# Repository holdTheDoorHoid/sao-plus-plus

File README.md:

# SAO++

Classic Simple Add-Ons, rebuilt for today's badges and for real production runs, plus a growing set of new ones.

The repo holds two kinds of board, kept in separate folders:

- **Ports** (`boards/`): other makers' SAOs, rebuilt to the SAO++ standard with credit to the original maker.
- **SAO++ Originals** (`originals/`): LSOH's own designs, made for SAO++ from scratch.

SAO++ takes older SAOs (the little art boards that plug into conference badges), ports them to the **SAO v1.69bis** 6-pin standard, adds small improvements where they make sense, and publishes them openly. Every board shares the same connector, power switch, battery holder, and LED family, so they can be built side by side on the same reels and the same assembly setup.

## What every SAO++ board has

- **6-pin SAO v1.69bis connector**, surface-mount and shrouded, on the back. Nothing pokes through the art side.
- **SAO / OFF / BATTERY switch**: runs from the badge or from its own CR2032. It is wired so the badge can never charge the coin cell.
- **CR2032 coin cell**: several days of daytime wear on a simple LED board.
- **Boards that need a chip** use a Seeed Studio XIAO ESP32 module instead of a coin cell: the same switch chooses between badge power and the module's own (USB-C or a LiPo).
- **LEDs on the back**: side-firing ones that light the art from the edges, or reverse-mount ones that shine through the board.
- **All parts on the back**; the front is pure art.

The full rules are in [docs/standard.md](docs/standard.md), and the shared parts with live prices are in [docs/parts.md](docs/parts.md).

## Layout

```
boards/<slug>/        one folder per PORT of another maker's SAO
originals/<slug>/     one folder per SAO++ ORIGINAL (LSOH's own design); same layout as a port
  board.yml           provenance, license, permission, features, shared parts used
  README.md           credit to the original maker, what changed, build notes
  hardware/           KiCad 10 project
  art/                source artwork
  production/         Gerbers, drill, BOM and placement files for one board and for a panel
  firmware/           only for boards with a microcontroller
boards/_template/     copy this to start a new board
lib/                  shared KiCad symbols, footprints, 3D models, power block, starter project
docs/                 house standard, approved parts, porting and permission guide
tools/                check_boards.py (paperwork check, runs on every push), gen_footprints.py, saopp_symbols.py,
                      gen_schematic.py, extract_outline.py, saopp_board.py (helpers for each board's build script), panelize.py, export_fab.py
```

## Ports

Other makers' SAOs, rebuilt. Credit and permission status are in each board's README.

| Board | Original maker | Status |
|---|---|---|
| [Fat Pika](boards/fat-pika/) | TwinkleTwinkie (DEF CON 26, 2018) | Designed and rule-checked, not yet built. **Permission pending: not open-licensed**, see the board README |
| [Mad Cat](boards/mad-cat/) | TwinkleTwinkie (DEF CON 26, 2018) | Designed and rule-checked, not yet built. **Permission pending: not open-licensed**, see the board README |
| [Big Green](boards/big-green/) | TwinkleTwinkie (DEF CON 26, 2018) | Designed and rule-checked, not yet built. **Permission pending: not open-licensed**, see the board README |
| [La Bomba](boards/la-bomba/) | TwinkleTwinkie (DEF CON 26, 2018) | Designed and rule-checked, not yet built. **Permission pending: not open-licensed**, see the board README |
| [Nibbler](boards/nibbler/) | TwinkleTwinkie (DEF CON 26, 2018) | Designed and rule-checked, not yet built. **Permission pending: not open-licensed**, see the board README |
| [RBG](boards/rbg/) | lemons4all (DEF CON 26, 2018) | Designed and rule-checked, not yet built. **Permission pending: not open-licensed**, see the board README |
| [Frida](boards/frida/) | lemons4all (DEF CON 26, 2018) | Designed and rule-checked, not yet built. **Permission pending: not open-licensed**, see the board README |
| [Oh My Glob (LSP)](boards/lumpy/) | lemons4all (DEF CON 26, 2018) | Designed and rule-checked, not yet built; the tightest fit of the set (see its README). **Permission pending: not open-licensed** |
| [Hack-Man](boards/hack-man/) | InstantArcade (Bob), 2024 | Recreated from the maker's pictures (no files were published), rule-checked, not yet built. Seeed XIAO ESP32 controller, new Rust firmware. **Permission pending: not open-licensed**, see the board README |
| [Han SAOlo](boards/han-saolo/) | davedarko (2024) | Designed and rule-checked, not yet built. Short life and weak green/blue on a coin cell (calculated). **Permission pending: not open-licensed**, see the board README |
| [Knight Rider (K.I.T.T.)](boards/knight-rider/) | davedarko (2017) | Designed and rule-checked, not yet built. No firmware yet. **Permission pending: not open-licensed**, see the board README |
| [Soot Sprite](boards/soot-sprite/) | davedarko (2026) | Designed and rule-checked, not yet built. **Permission pending: not open-licensed**, see the board README |
| [COVID-19 Test](boards/covid-test/) | davedarko (2022) | Designed and rule-checked, not yet built. **Permission pending: not open-licensed**, see the board README |
| [Penghito Poco](boards/penghito-poco/) | davedarko (year not recorded) | Designed and rule-checked, not yet built. **Permission pending: not open-licensed**, see the board README |
| [Mysterio](boards/mysterio/) | davedarko (2025) | Designed and rule-checked, not yet built. Seeed XIAO ESP32 controller, new Rust firmware (never run on hardware). **Permission pending: not open-licensed**, see the board README |
| [Do Or Donut](boards/do-or-donut/) | davedarko (2019) | Designed and rule-checked, not yet built. Seeed XIAO ESP32 controller, new Rust firmware (never run on hardware). **Four-layer board.** **Permission pending: not open-licensed**, see the board README |
| [Vendetta](boards/vendetta/) | davedarko (2022) | Designed and rule-checked, not yet built. Scaled up 1.23x. **Permission pending: not open-licensed**, see the board README |
| [Hello My Name Is](boards/hello-my-name-is/) | davedarko (2024) | Designed and rule-checked, not yet built. Scaled up 1.1x. **Permission pending: not open-licensed**, see the board README |
| [LECCO postcard](boards/lecco/) | davedarko (2026) | Designed and rule-checked, not yet built. Scaled up 1.2x; badge power only (no cell or switch). **Permission pending: not open-licensed**, see the board README |
| [Sloth](boards/sloth/) | davedarko (2017) | Was a pin; now an SAO. Designed and rule-checked, not yet built. Scaled up 1.3x. No firmware yet. **Permission pending: not open-licensed**, see the board README |
| [Flux Capacitor](boards/flux-capacitor/) | davedarko (2017) | Was a pin; now an SAO. Designed and rule-checked, not yet built. Scaled up 1.35x. No firmware yet. **Permission pending: not open-licensed**, see the board README |
| [Retro Spacehuhn](boards/spacehuhn/) | davedarko (year not recorded) | Was a pin; now an SAO. Designed and rule-checked, not yet built. The chicken logo is Spacehuhn's. **Permission pending: not open-licensed**, see the board README |
| [Mr. Robot](boards/mr-robot/) | davedarko (2019) | Designed and rule-checked, not yet built. Scaled up 1.1x. Seeed XIAO ESP32 controller, new sounder driver, new Rust firmware (never run on hardware). **Permission pending: not open-licensed**, see the board README |
| [Nunchuck](boards/nunchuck/) | Andrew Geppert / ageppert (2024) | Designed and rule-checked, not yet built. Badge-driven adapter for a Wii Nunchuk: no chip, no switch, no cell. Rust host driver crate. MIT (open licence) |
| [Mad Cat Backpack](boards/mad-cat-backpack/) | Peter Shabino / Wireb (2018) | Designed and rule-checked, not yet built. Sits behind a bare SAO++ Mad Cat and animates its eyes and teeth. Seeed XIAO ESP32 controller, new Rust firmware (never run on hardware). MIT (open licence) |
| [Duck Bath](boards/duck-bath/) | Adrian Studer / astuder (2024) | Designed and rule-checked, not yet built. Scaled up 1.45x. Seeed XIAO ESP32 controller, new Rust firmware (never run on hardware). MIT (open licence) |
| [TARS](boards/tars/) | davedarko (2024) | Designed and rule-checked, not yet built. Display, touch slabs and speaker kept; Seeed XIAO ESP32 controller plus a touch chip, new Rust firmware (never run on hardware). MIT (open licence) |
| [Eggplant](boards/eggplant/) | Krux / Darknet Industries (2018) | Designed and rule-checked, not yet built. Scaled up 1.35x. Seeed XIAO ESP32 controller, new Rust firmware (never run on hardware). MIT (open licence) |

## SAO++ Originals

LSOH's own designs, under the SAO++ licences. None is built yet; the first shortlist of ten
cybersecurity-themed art boards is in [originals/README.md](originals/README.md).

## Adding a board

Read [docs/porting-guide.md](docs/porting-guide.md). In short: confirm the license or get the maker's permission **first**, copy `boards/_template` (into `originals/<slug>/` for an LSOH design, with `permission: own`), start from `lib/template`, and run `python3 tools/check_boards.py`.

## License

- Hardware designs: [CERN-OHL-S-2.0](LICENSE). Anyone can build and sell these; changes you distribute must stay open.
- Artwork: [CC-BY-SA-4.0](LICENSE-ART).
- **These licenses cover SAO++'s own work only**, which includes every board in `originals/` in full. A board marked "permission pending" in its README is not open-licensed: its original design and art stay with the original maker.
- Boards ported from other makers keep their credit, and their original license terms are recorded in each `board.yml`. Where a board's original license differs, its README says so and it takes precedence for that board.

Original designs remain credited to their makers. If you made one of these boards and want it changed or removed, open an issue.

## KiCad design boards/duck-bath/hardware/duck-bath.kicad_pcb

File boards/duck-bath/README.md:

# Duck Bath — SAO++ edition

Originally **duckBATH**, one of the two **duckGLOW** SAOs by **Adrian Studer (astuder)**, 2024: https://github.com/astuder/duckglow (write-up: https://hackaday.io/project/198918-duckglow-sao). A bathtub full of bubbles with a 5 mm RGB LED standing in the foam; a little rubber duck sits on the LED and glows. Its sister board, the shark-mouth **Duck Jaws**, is in [`../duck-jaws/`](../duck-jaws/).

> **Open licence — credit kept.** The maker's repository is MIT-licensed: "MIT License, Copyright (c) 2024 Adrian Studer". The same `LICENSE.md` also carries the full text of the CERN Open Hardware Licence v2 – Permissive (CERN-OHL-P), without saying which part applies to what; both are permissive. His licence file is kept unchanged in [`original/LICENSE.md`](original/LICENSE.md), and this note records what was changed (CERN-OHL-P section 3.3 asks for that): on 2026-11-11 the board was rebuilt for SAO++ as listed below, and the firmware was rewritten in Rust. Nothing else is needed before publishing.
>
> The art is the maker's own drawing; nothing on the board belongs to a third party. The rubber duck is a separate, bought toy.

The renders use green; the maker's boards are **white with black silkscreen** (see `production/README.md`).

## What changed from the original

| | Original (2024, v0.2) | SAO++ rev A |
|---|---|---|
| Size | 40.3 × 20.3 mm | **Scaled up 1.45×** (outline and drawing together): **58.1 × 29.0 mm** (see "Why it is 45 % bigger") |
| The LED | 5 mm RGB LED standing in the bubbles, legs soldered on the back | **Same LED, same footprint, true size**, centred where it was |
| Controller | WCH CH32V003 chip with a boost converter (runs from 2–3.3 V) | **Seeed Studio XIAO ESP32** module soldered flat on the back (C3, S3 or C6 all fit). Its USB-C socket comes out of the tub bottom, between the feet |
| Connector | 2×3 SMD pin header | 6-pin SAO v1.69bis, shrouded and keyed, under the LED, 5.7 mm left of the middle |
| Power | Badge only | Slide switch, knob out of the tub bottom: **SAO** / **OFF** / **USB-BAT** (USB-C, or a LiPo cell on the new JST-PH socket at the left wall, which the XIAO charges) |
| Front | Copper pour under the mask, silkscreen drawing of tub, bubbles and feet | All kept, scaled. Two 0.9 mm holes in the tub bottom (the switch's pegs), four small covered holes (ground vias) in the tub, and the tub bottom is cut flat by at most 0.5 mm over 11 mm under the switch so its knob sticks out |
| Back | Board name, I2C address and GPIO notes, address jumpers | Board name, "SAO++ rA", "Adrian Studer 2024", "NO USB ON SAO", switch ends (SAO / USB), "+"/"−" and "LiPo" at the socket, "1" at the connector |
| Dropped | — | CH32V003, boost converter (ME2188 + 22 µH + three 22 µF), reverse-polarity transistor, two 10 k I2C pull-ups (SAO++ boards leave the pull-ups to the badge), 1 k on GPIO1, 100 nF, two address jumpers, test pad |

**Parts shared with the rest of SAO++:** connector, switch, XIAO footprint, LiPo socket, 330 Ω resistor. **New, kept in this board's folder:** the maker's 5 mm RGB LED and his 100 Ω LED resistor (three of them). The 100 Ω is kept rather than the shared 330 Ω because green and blue need about 3 V: through 330 Ω from a 3.3 V rail they would barely glow. The LED itself has no part number in the maker's files: one must be picked (any 5 mm, 4-leg, common-anode RGB LED with legs in the order red, anode, green, blue).

## Why it is 45 % bigger (owner rule of 2026-11-12)

The maker's tub is 20 mm tall; the XIAO alone is 21 mm long and 18 mm wide, and its USB-C plug (about 12.4 mm wide) must reach a straight bit of edge. The only straight edges are the tub bottom between the feet and the short side walls. Tried in 5 % steps:

- USB-C out of a side wall: needs about 1.52×, and the rim's little bulge then blocks the plug.
- USB-C out of the bottom, module under the LED: needs 1.55× (the module must clear the LED's legs).
- **USB-C out of the bottom, module beside the LED: fits at 1.45×** with 0.2 mm to spare between the module and the LED's legs on one side and the plug and the right foot on the other. 1.40× does not fit.

The connector, switch and LiPo socket then fit beside it. Board area is 2.1× the original. Line widths only get thicker.

## How it is wired (all on the back, no signal vias)

Everything electrical is on the back copper; nothing but the maker's art is on the front. Three tricks keep it to one layer:

- **Under the module.** Two wires (SCL and GPIO2) slip between the XIAO's edge pads, 0.17 mm from each (as on Mr. Robot), and reach their pads from underneath, so they never cross SDA. The battery wire also runs under the module to its two pad sets.
- **Resistors as bridges.** The badge's 3.3 V runs between the pads of R4 (OFF sense), and the 3.3 V for the LED runs between the pads of R1 (red resistor).
- **Ground on the front.** The front copper (the maker's pour) is joined to ground through **four tented vias**, which also joins up the bits of back ground that the wires cut apart. They show as four tiny dots on the white tub, like the dots on the maker's own board.

## Pin map

| XIAO pin | Goes to |
|---|---|
| D10 | red: R1 100 Ω → LED red leg. Low = on |
| D8 | green: R2 100 Ω → LED green leg. Low = on |
| D7 | blue: R3 100 Ω → LED blue leg. Low = on |
| D4 / D5 | SAO SDA / SCL (no pull-ups on the board; the badge provides them). The XIAO is the badge's I2C target |
| D6 | SAO GPIO2 through 330 Ω (R6): WS2812 data from the badge, as on the maker's board |
| D1 | switch OFF sense, through R4 (330 Ω): high when the knob is on OFF |
| 3V3, GND | the board's 3.3 V rail (switch common, LED anode) and ground |
| BAT+ / BAT− (under the module, both positions) | the JST-PH LiPo socket |
| D0, D2, D3, D9, 5V | not connected |
| SAO GPIO1 | **not connected** (see below) |

**Why D7 and D8, and no SAO GPIO1.** Only D10 and D3 are free, non-start-up pins on all three modules, and the LED needs three. The LED sits right above the gap between the connector and the XIAO's left-hand pads, where SDA, SCL and GPIO2 already cross, so its wires go round the top of the module to the right-hand pads: D7, D8, D10 and 3V3, in that order. That takes D7, the house pin for SAO GPIO1. The maker used GPIO1 only to program his chip, so nothing is lost on this board. D8 is a start-up ("strapping") pin on the C3: the LED pulls it up weakly at power-on, which is the level the C3 wants, but see the checklist.

## Current budget (badge power)

| | About | Note |
|---|---|---|
| XIAO, radio off, 80 MHz | 20–25 mA (C3/C6), more on the S3 | the firmware never starts Wi-Fi or Bluetooth |
| Red at full | 13 mA | (3.3 V − 2.0 V) / 100 Ω; LED forward voltages are typical values, not measured |
| Green, blue at full | 3–4 mA each | they need about 3 V, so little current flows from 3.3 V |
| **All white, full** | **about 45 mA** | inside the 50 mA SAO++ budget, just |
| Maker's default animation | about 25–30 mA | red and green breathing up to 31 %, blue off |

## Firmware

New Rust firmware for the XIAO is in [`firmware/`](firmware/), shared with Duck Jaws (43 tests pass; builds for the C3, C6 and S3; **never run on a real board**). It keeps the maker's I2C register map (badge code written for his boards works), his fading animation and default colours, his WS2812 mode on GPIO2, and saving settings to flash. It answers at **0x22** (house numbering), or the maker's **0x6C** as a build option. See its README for what is the same and what is not.

## Things to check on the first prototype

1. **Badge power into the XIAO's 3V3 pin**: boots from a badge alone, nothing warm, current under 50 mA with the LED white.
2. **LED colours and brightness** through the rubber duck, with the maker's 100 Ω; the duck should glow as in the maker's photos.
3. **D8 at start-up (C3):** flashing over USB and normal start-up must still work with the green LED on D8. If holding BOOT while plugging in no longer enters download mode, D8 needs a pull-up (a 1.3 k from D8 to 3V3 would do, at the cost of 2.5 mA when green is on).
4. **The wires between the XIAO's pads** (0.17 mm gaps): check for solder bridges after assembly, as on Mr. Robot.
5. **USB-C plug fit** at the tub bottom: the socket sticks out about 0.5 mm past the edge at its middle; the plug must seat fully.
6. **Switch knob** at the flattened tub bottom: it should slide with a fingernail; if SAO and USB turn out swapped, the silkscreen is wrong, not the wiring.
7. **LiPo polarity**: the socket follows the Adafruit / SparkFun convention, "+" printed beside it.
8. **Connector position and pin 1** against a v1.69bis badge, and how the wider board hangs with the connector 5.7 mm left of centre.
9. **The four ground vias** on the front: should be barely visible on a white board.

## Files

- `hardware/duck-bath.kicad_pro`: KiCad 10 project. ERC: 0. DRC: 0 errors, 0 unconnected, schematic matches the board; 2 warnings (the LED's "B G + R" leg label touching the connector's unused pin 5, and one copper-sliver warning in the art).
- `hardware/circuit.json` (written by `make_circuit.py`): the circuit as data; `tools/gen_schematic.py duck-bath` and `build_board.py` both read it.
- `hardware/extract_art.py`: pulls the outline, the front drawing and the LED position out of the maker's KiCad 8 board into `hardware/art.json`.
- `hardware/build_board.py`: rebuilds the whole board in one run (about 30 s): placement, the hand-routed wires, the battery / 3.3 V / ground routing by `router.py` (a copy of Knight Rider's small grid router), ground copper, labels.
- `hardware/parts_local.py`, `hardware/make_local_footprints.py`, `hardware/duck-bath-local.pretty/`: the LED and the 100 Ω resistor.
- `hardware/duck-bath.kicad_dru`: the art rule, plus three small parts allowed inside bigger parts' courtyards (each with its real gap).
- `production/`: everything a board house needs. Start with [production/README.md](production/README.md).
- `original/`: the maker's untouched files: KiCad 8 design, firmware (C), examples, design SVGs, licence.

## Parts cost (parts only, LCSC list prices checked 2026-11-10 unless noted)

| Part | Qty | Each @ ~100 boards |
|---|---|---|
| Connector XFCN BH254VS-6P (C492445) | 1 | $0.12 |
| Switch C&K PCM13SMTR (Digikey) | 1 | ~$0.90 |
| LiPo socket JST S2B-PH-SM4-TB (C295747) | 1 | $0.16 |
| Resistor 330 Ω 0603 (C23138) | 2 | <$0.01 |
| Resistor 100 Ω 0603 (maker's C22775) | 3 | not priced (orchestrator to check) |
| 5 mm RGB LED, common anode | 1 | not chosen yet |
| **Total without the module, LED and 100 Ω** | | **about $1.20** |
| Seeed Studio XIAO ESP32-C3 / S3 / C6 | 1 | not priced here |

The bare board, the rubber duck and the optional LiPo cell are not included.

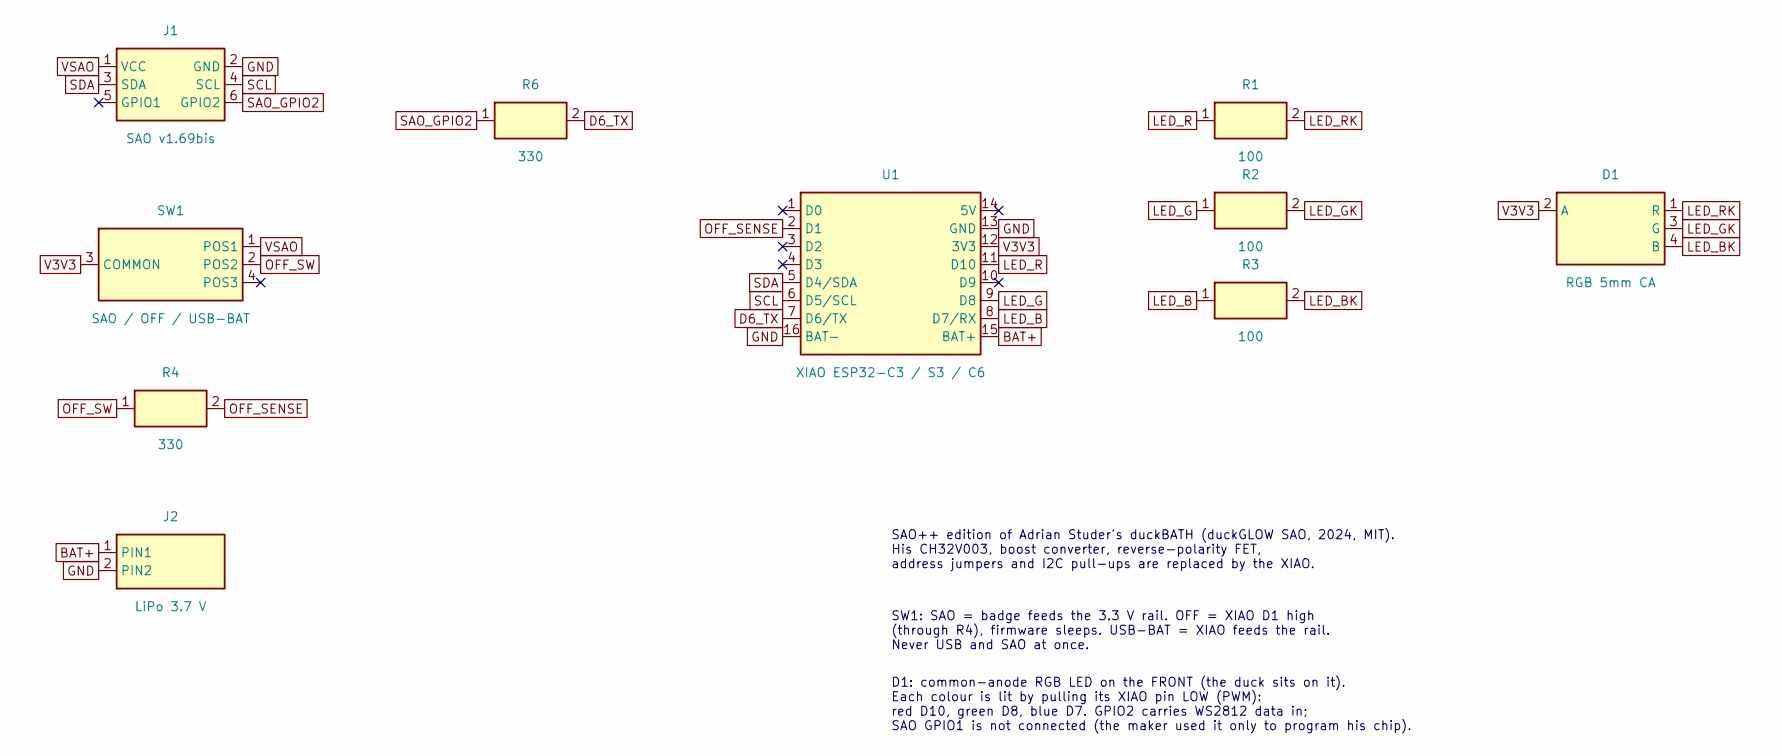
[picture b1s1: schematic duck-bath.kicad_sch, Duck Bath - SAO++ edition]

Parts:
D1: RGB 5mm CA; LED_D5.0mm-4_RGB_single-side; MPN 5 mm RGB LED, common anode, 4 legs, R-A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
J1: SAO v1.69bis; SAOPP_CONN-01_BoxHeader_2x03_P2.54mm_SMD_XFCN_BH254VS-6P; MPN BH254VS-6P; LCSC C492445
J2: LiPo 3.7 V; SAOPP_CONN-10_JST_PH_S2B-PH-SM4-TB_1x02_Horizontal; MPN S2B-PH-SM4-TB(LF)(SN); LCSC C295747
R1, R2, R3: 100; R_0603_1608Metric; MPN 0603WAF1000T5E; LCSC C22775
R4, R6: 330; SAOPP_R_0603_1608Metric; MPN 0603WAF3300T5E; LCSC C23138
SW1: SAO / OFF / USB-BAT; SAOPP_SW-01_Slide_SP3T_CK_PCM13SMTR; MPN PCM13SMTR; LCSC C221842
U1: XIAO ESP32-C3 / S3 / C6; SAOPP_MCU-01_Seeed_XIAO_SMD_C3_S3_C6; MPN XIAO ESP32-C3 / S3 / C6

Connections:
BAT+: J2.1 (PIN1), U1.15 (BAT+)
D6_TX: R6.2, U1.7 (D6/TX)
GND: J1.2 (GND), J2.2 (PIN2), U1.13 (GND), U1.16 (BAT-)
LED_B: R3.1, U1.8 (D7/RX)
LED_BK: D1.4 (B), R3.2
LED_G: R2.1, U1.9 (D8)
LED_GK: D1.3 (G), R2.2
LED_R: R1.1, U1.11 (D10)
LED_RK: D1.1 (R), R1.2
OFF_SENSE: R4.2, U1.2 (D1)
OFF_SW: R4.1, SW1.2 (POS2)
SAO_GPIO2: J1.6 (GPIO2), R6.1
SCL: J1.4 (SCL), U1.6 (D5/SCL)
SDA: J1.3 (SDA), U1.5 (D4/SDA)
V3V3: D1.2 (A), SW1.3 (COMMON), U1.12 (3V3)
VSAO: J1.1 (VCC), SW1.1 (POS1)

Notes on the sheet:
SAO++ edition of Adrian Studer's duckBATH (duckGLOW SAO, 2024, MIT). His CH32V003, boost converter, reverse-polarity FET, address jumpers and I2C pull-ups are replaced by the XIAO.
SW1: SAO = badge feeds the 3.3 V rail. OFF = XIAO D1 high (through R4), firmware sleeps. USB-BAT = XIAO feeds the rail. Never USB and SAO at once.
D1: common-anode RGB LED on the FRONT (the duck sits on it). Each colour is lit by pulling its XIAO pin LOW (PWM): red D10, green D8, blue D7. GPIO2 carries WS2812 data in; SAO GPIO1 is not connected (the maker used it only to program his chip).

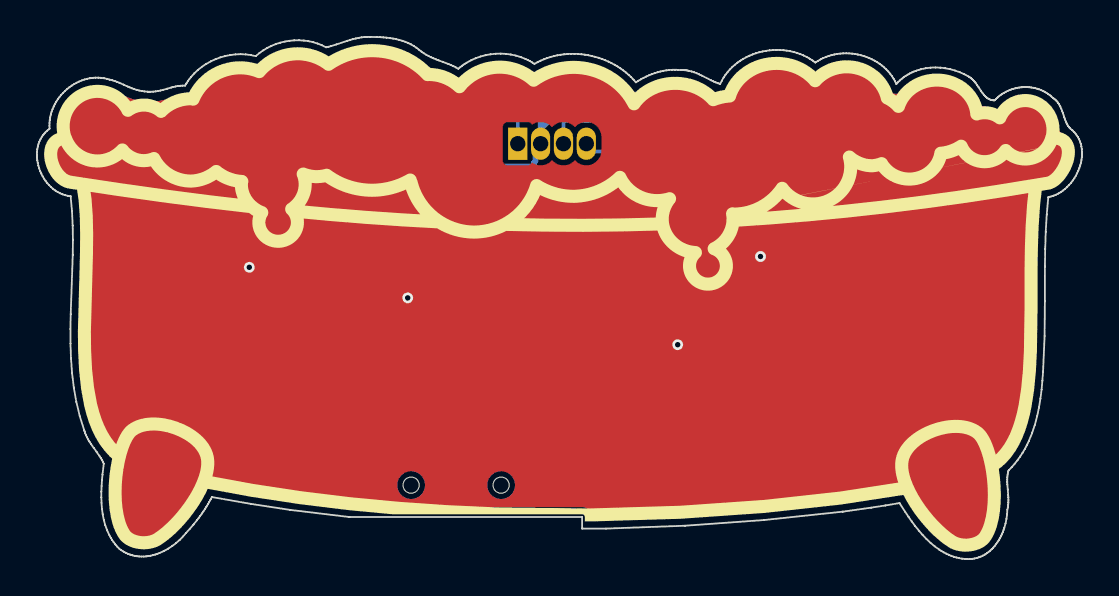
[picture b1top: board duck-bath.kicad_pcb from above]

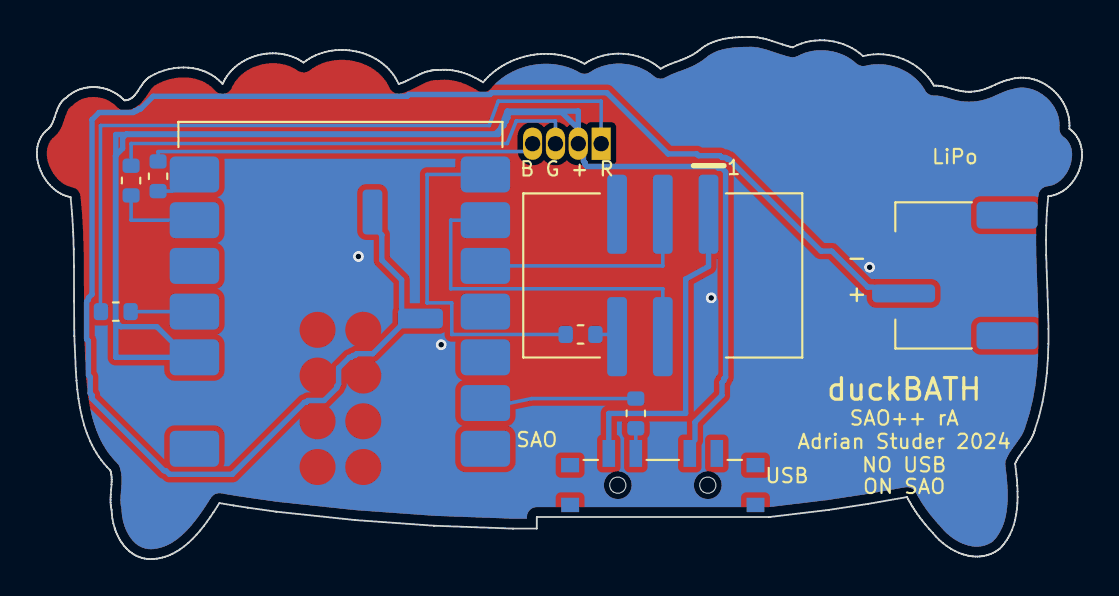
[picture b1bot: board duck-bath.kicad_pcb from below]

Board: 2 copper layers, 58.1 x 29.0 mm, 10 parts (9 on the bottom side), 16 nets.

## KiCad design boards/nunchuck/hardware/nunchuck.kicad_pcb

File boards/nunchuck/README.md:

# SAO Nunchuck — SAO++ edition

Originally the **SAO Nunchuck V1.0** by **Andy and Jared Geppert** (GitHub `ageppert`, Machine Ideas), 2024: https://github.com/ageppert/SAO_Nunchuck (commit 6b02ca0), project page https://hackaday.io/project/198000-sao-nunchuck

> **Open licence (MIT).** The maker's repository is under the MIT licence: *Copyright (c) 2024 Andrew Geppert*. The full notice is kept unchanged in [original/LICENSE.md](original/LICENSE.md) and must travel with these files. No permission request is needed. (The board's own lettering credits Andy and Jared Geppert; the licence file names Andrew Geppert as the copyright holder.)
>
> **The controllers belong to someone else.** The front shows a Wii Remote and a Wii Nunchuk swung like nunchaku, and the board exists to plug in a Wii Nunchuk. Those two shapes are Nintendo product designs, and *Wii* and *Nunchuk* are Nintendo trademarks. The MIT licence covers the Gepperts' drawing and board, not Nintendo's rights: anything sold needs its own check.

A 38 × 51 mm board that lets a badge use a **Wii Nunchuk** (stick, two buttons, motion sensor) as a game controller. The Nunchuk's own cable plug slides onto a gold-fingered tongue at the top. Two **Qwiic** sockets pass the same connection on to other small I2C boards.

## This board has no switch, no battery and no chip — on purpose

Most SAO++ boards get the SAO / OFF / BAT switch and a coin cell. This one does not, because it would have nothing to run:

- There is **no chip on the board**. The Nunchuk *is* the device: the badge's own processor talks to it over the SAO connector's two I2C wires, at address 0x52 (fixed by the Nunchuk; nothing on this board can change it).
- A coin cell would only light the Nunchuk up with nobody listening.
- A XIAO controller would turn a simple adapter into a second computer that has to pass every reading on to the badge. The maker designed it as a plain adapter, and that is what a badge expects.

So the board is **badge-driven**: SAO pin 1 (3.3 V) goes straight to the Nunchuk and to both Qwiic sockets. That is a recorded exception to the house rule that pin 1 only goes to the power switch. There is no cell on the board, so nothing can ever push current into one.

The software half of this board is therefore **a driver for the badge**, not firmware for the board: see [firmware/README.md](firmware/README.md).

## What changed from the maker's board

| | Maker's 2024 board | SAO++ rev A |
|---|---|---|
| Size | 38.1 × 50.8 mm (1.5 × 2 in) | The same. Not scaled |
| Nunchuk tongue | Gold fingers on both sides of a tongue cut into the top edge | **Exactly the same**: outline, slots, fingers, place, true size |
| SAO connector | 2×3 through-hole header, plus gold fingers along the bottom edge so the board could also be pushed straight into a badge's socket | The shared shrouded, keyed SMD connector J1 on the back, key slot toward the tongue, same centre line, 1.5 mm higher. The bottom-edge fingers and the six holes are gone (see below) |
| Qwiic sockets | Two, top left and right, openings at the side edges | The same two, same places. Their metal tabs now go to ground |
| Wiring | 16 open vias; tracks on both sides, including a visible band of lines on the front under the tongue | **8 vias, covered by solder mask on both sides**; three tracks down the back; short links on the front in the same band under the tongue, where the maker had his |
| Ground | No ground copper | Back copper is ground, kept off the tongue |
| Front art | Copper-and-gold Wii Remote, Nunchuk and chain | Unchanged |
| Back lettering | "Address 0x52 (decimal 82)", "SAO NUNCHUCK", Machine Ideas logo, "Designed by Andy and Jared Geppert www.MachineIdeas.com", "Manufactured by PCBX.COM", "2024", "V1.0" | All kept, same words, size and place, and now in **the maker's exact letter shapes** (see below). New small labels: "1" at pin 1, "SAO++ rA", "Qwiic" at each socket |

### Why the bottom-edge fingers went

The maker's header doubled as a card-edge plug: gold fingers on the bottom edge let the board go straight into a badge's 2×3 socket with no header fitted. SAO++ uses one shrouded, keyed connector on every board, so a board cannot go in backwards or one row off. Keeping the fingers as well would put copper on the front and need a hard-gold edge. **Owner's call** if you want them back as an extra: they cost nothing in parts, but would add front copper at the bottom edge and two or three more vias.

### Why there are vias at all

A Nunchuk plug touches the tongue from both sides, so two of its five fingers (clock and ground) are on the front: those two vias would be needed anyway. The other six come from the two Qwiic sockets. Each carries the same four wires in the same order, and placed as mirror images they cross over each other (two identical sockets on the same side of a board always need a crossing somewhere). The crossings are short links on the front, in the dark strip between the tongue and the chain, where the maker ran his own front tracks. All eight vias are 0.3 mm holes, covered by mask, in that strip.

### The lettering

The maker set his back lettering in TrueType fonts (Apple Chancery for "SAO NUNCHUCK", Comic Sans MS for the rest). Most computers and factories do not have those fonts, and KiCad then draws the text in a substitute that is wider: "SAO NUNCHUCK" ran off both sides of the board. His file also stores the letters exactly as his own computer drew them, and those match his 2024 factory files. Those exact shapes are used, so the lettering looks as he made it, on any machine.

"Manufactured by PCBX.COM" is the maker's thank-you to the factory that sponsored his batch. It is kept unchanged as his credit; **owner's call** whether to keep it on boards made elsewhere.

## Power

Everything runs from the badge's 3.3 V: the Nunchuk, plus whatever is plugged into the two Qwiic sockets. The board adds no load of its own.

- **Nunchuk current: not measured here.** It is commonly reported as a few milliamps; measure it on the prototype.
- **Qwiic sockets:** anything plugged in draws from the same SAO pin. SAO++ budgets 50 mA per add-on; a Qwiic display or LED board can exceed that on its own. The README for users should say so.
- **3.3 V only.** A genuine Nunchuk runs at 3.3 V. Nothing here makes 5 V.
- **No pull-up resistors on this board** (as the SAO standard asks: the badge provides them). Some Qwiic boards carry their own; with several chained the bus gets stiffer, which is usually fine.

## Parts

| Ref | Part | Where | Note |
|---|---|---|---|
| J1 | SAOPP-CONN-01 shrouded SMD SAO connector (shared) | back, bottom middle | |
| J2 | Wii Nunchuk tongue | the top edge | Gold fingers on the board itself: nothing to buy or place, not in the BOM |
| J3, J4 | JST SH 4-pin side-entry socket (Qwiic), **SM04B-SRSS-TB(LF)(SN)** | back, top right and top left | Local part; LCSC number not filled in yet |

Footprints: J2 is the maker's own tongue footprint, cut out of his board file (its outline lines are now part of the board outline). J3/J4 use KiCad's stock JST SH footprint, the same pattern the maker used.

## Rule checks (as built)

- Schematic (ERC): 0 problems.
- Board (DRC, with schematic check): 0 errors, 0 warnings, 0 unconnected, 0 schematic mismatches.
- 4-up panel: 0 errors, 0 warnings, 0 unconnected.
- One extra rule (`hardware/nunchuck.kicad_dru`): the tongue's fingers run to within 0.19 mm (back) and 0.14 mm (front) of the tongue tip, as the maker drew them; the plug has to reach them. Every other pad is at least 0.25 mm from the edge.

## What only a prototype can tell us

1. **That a real Nunchuk plug fits the tongue and latches.** It is the maker's tongue unchanged, so it should, but it has not been tried on an SAO++ board. Ask the factory for **1.6 mm** board and ENIG finish; the tongue's width and slots are milled, so check the factory can mill the 1 mm side notches.
2. That the badge reads the Nunchuk through J1 (key slot up, VCC top-left seen from the front) with the badge's own pull-ups.
3. The Nunchuk's current from the badge's 3.3 V, and whether a clone Nunchuk behaves the same as a genuine one.
4. That a Qwiic board plugged into either socket works at the same time.
5. That the front links and vias in the strip under the tongue are as unobtrusive as the maker's own tracks were.

## Files

- `hardware/build_board.py` rebuilds `hardware/nunchuck.kicad_pcb` from the maker's file in one run; `hardware/make_local_footprints.py` writes the two local footprints; `hardware/circuit.json` is the circuit (the schematic is generated from it by `tools/gen_schematic.py`, then `hardware/fix_schematic.py` marks the tongue "not in BOM").
- `production/` has the ordering files and their notes.
- `firmware/nunchuck-driver/` is the badge-side Rust driver.
- `original/` is the maker's repository as published (large binaries left out), with his MIT licence.

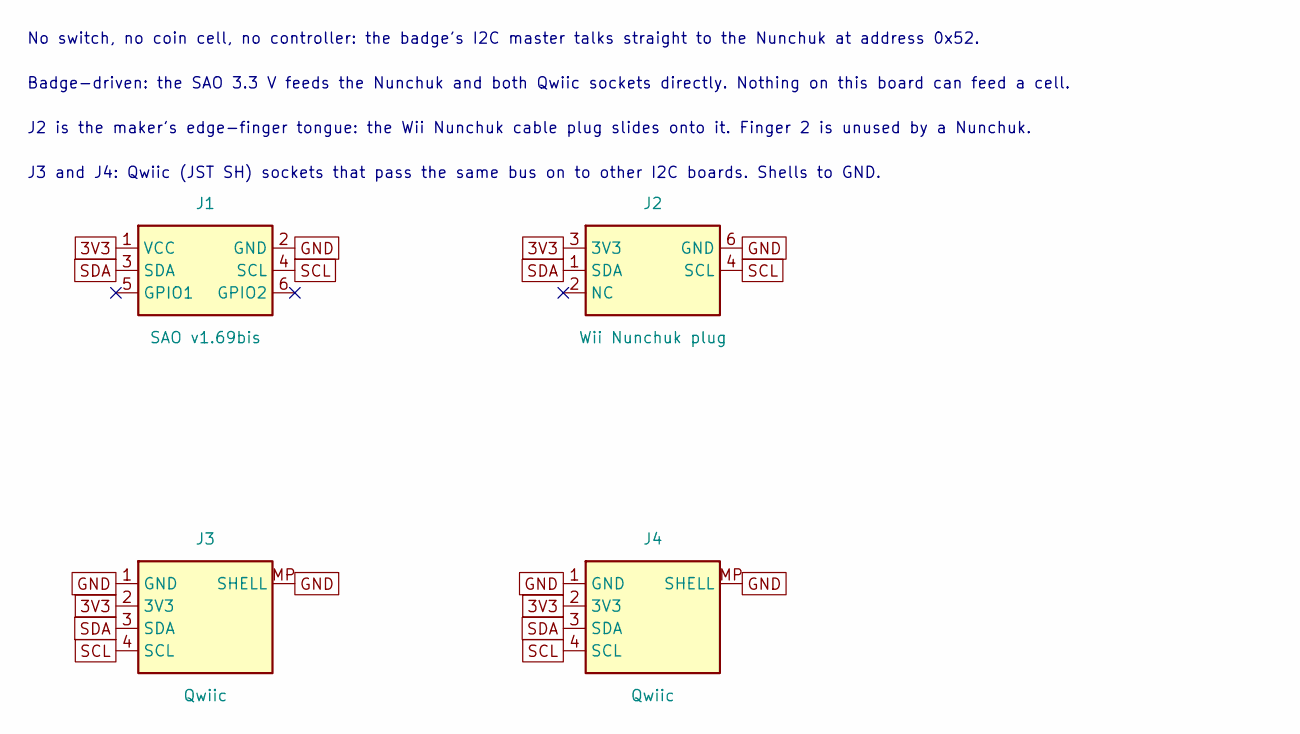
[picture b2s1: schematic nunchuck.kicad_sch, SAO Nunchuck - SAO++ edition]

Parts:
J1: SAO v1.69bis; SAOPP_CONN-01_BoxHeader_2x03_P2.54mm_SMD_XFCN_BH254VS-6P; MPN BH254VS-6P; LCSC C492445
J2: Wii Nunchuk plug; Nunchuk-male; MPN none: edge fingers on the board itself
J3, J4: Qwiic; JST_SH_SM04B-SRSS-TB_1x04-1MP_P1.00mm_Horizontal; MPN SM04B-SRSS-TB(LF)(SN); LCSC C160404

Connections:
3V3: J1.1 (VCC), J2.3 (3V3), J3.2 (3V3), J4.2 (3V3)
GND: J1.2 (GND), J2.6 (GND), J3.1 (GND), J3.MP (SHELL), J4.1 (GND), J4.MP (SHELL)
SCL: J1.4 (SCL), J2.4 (SCL), J3.4 (SCL), J4.4 (SCL)
SDA: J1.3 (SDA), J2.1 (SDA), J3.3 (SDA), J4.3 (SDA)

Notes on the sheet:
No switch, no coin cell, no controller: the badge's I2C master talks straight to the Nunchuk at address 0x52.
Badge-driven: the SAO 3.3 V feeds the Nunchuk and both Qwiic sockets directly. Nothing on this board can feed a cell.
J2 is the maker's edge-finger tongue: the Wii Nunchuk cable plug slides onto it. Finger 2 is unused by a Nunchuk.
J3 and J4: Qwiic (JST SH) sockets that pass the same bus on to other I2C boards. Shells to GND.

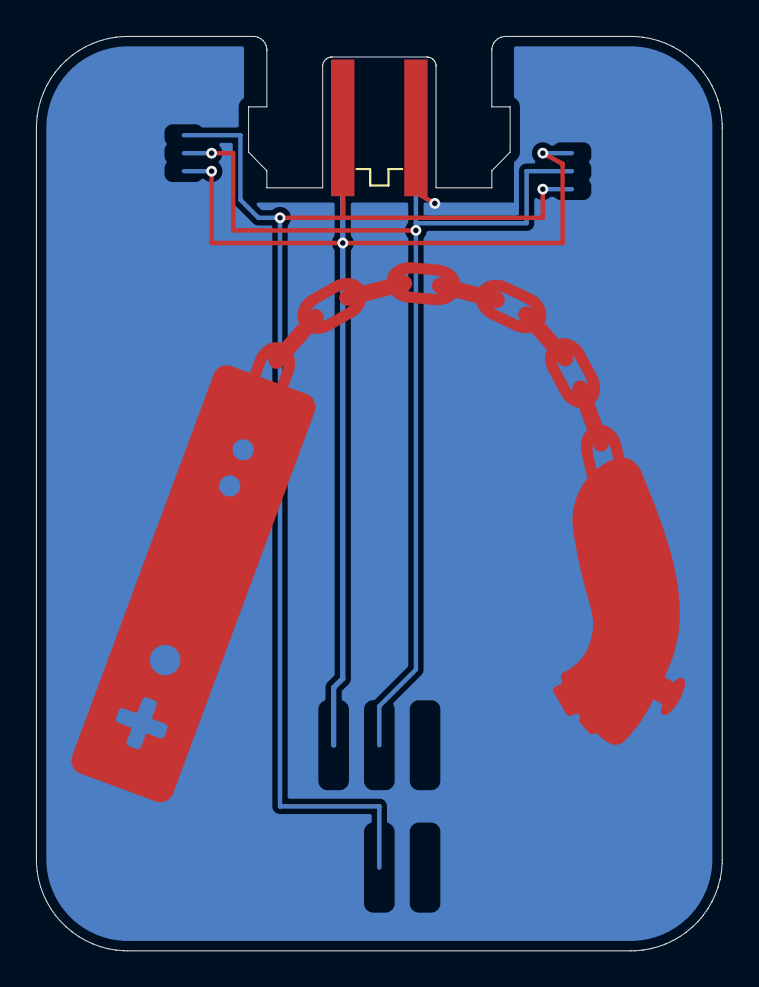
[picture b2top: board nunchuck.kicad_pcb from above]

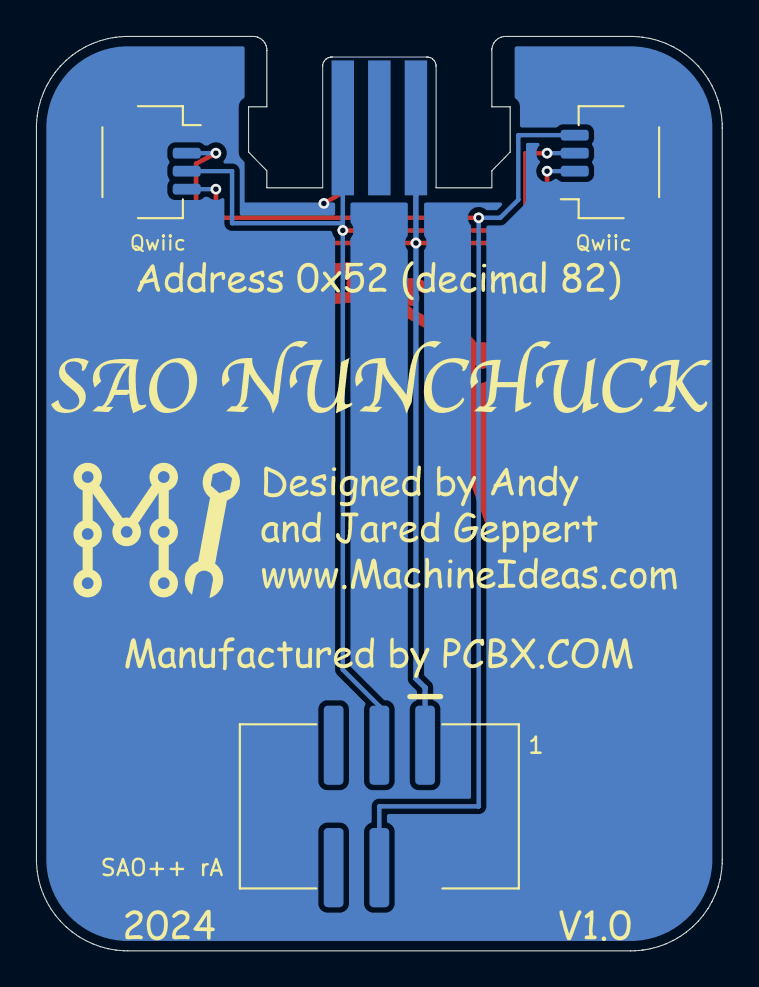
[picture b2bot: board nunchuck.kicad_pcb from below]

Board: 2 copper layers, 38.1 x 50.8 mm, 5 parts (4 on the bottom side), 4 nets.

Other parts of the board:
L1: Machine_Ideas_logo

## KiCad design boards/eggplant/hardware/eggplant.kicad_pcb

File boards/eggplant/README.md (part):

# Eggplant — SAO++ edition

Originally the **DC Darknet "Official" Eggplant Emoji Shitty Add-on** by **thedarknet (Darknet Industries)**, designed by **Krux**, for DEF CON 26 (2018): https://github.com/thedarknet/dc26-badge/tree/63ec6ed/hardware/dc26-sao/eggplant (firmware: `dc26-sao/eggplant`). An eggplant-shaped add-on with five blue/red LEDs that fade in purple patterns, an I2C "memory" with a name and serial number, and an infection game badges can play with it.

> **Open licence — credit kept.** The maker's repository is MIT-licensed: "MIT License, Copyright (c) 2017" (the notice gives no name; the sketch says "Designed by Krux - 2018"). His licence file is kept unchanged in [`original/LICENSE`](original/LICENSE), and his credit block, "krux was here" and his base64 line are all still printed on the back. No permission is needed to publish. On 2026-11-12 the board was rebuilt for SAO++ as listed below and the firmware was rewritten in Rust (also MIT, see [`firmware/README.md`](firmware/README.md)).
>
> The art is the maker's own drawing of the eggplant emoji; nothing on the board belongs to a third party.

## What changed from the original

| | Original (2018) | SAO++ rev A |
|---|---|---|
| Size | 27.6 × 55.9 mm | **Scaled up 1.35×** (outline and art together): **37.3 × 75.4 mm** (see "Why it is 35 % bigger") |
| Controller | ATtiny85 | **Seeed Studio XIAO ESP32** module soldered flat on the back (C3, S3 or C6 all fit), across the round bottom, USB-C out of the left-hand side |
| Connector | 2×2 SMD header (old 4-pin SAO), turned 45° | 6-pin SAO v1.69bis, shrouded and keyed, in the upper body, **turned 45° the same way**, so the eggplant still hangs leaning like the emoji |
| Power | Badge only | Slide switch, knob out of the right-hand side of the bulb: **SAO** / **OFF** / **USB-BAT** (USB-C, or a LiPo cell on the new JST-PH socket below the switch, which the XIAO charges) |
| LEDs | Five blue/red two-colour LEDs on the back, every blue on one ATtiny pin and every red on another, 22 Ω each | **Same LEDs, same land pattern**, same wiring (blue on XIAO D3, red on D2), one resistor per colour per LED: **330 Ω for blue, 1.3 k for red** (the shared values; see "LED current") |
| Front | Bare-gold stem and calyx, body copper under the mask, a copper-free light stripe down the left, leaf and highlight in silkscreen | All kept, scaled. His body copper (it was his ground pour) is now the ground plane. **33 tiny covered holes (vias)** sit in it, and 9 short covered links run under the mask (see "How it is wired"). Two 0.9 mm holes for the switch pegs. The bulb's right-hand side is **cut flat by at most 0.71 mm over 13 mm** where the switch knob comes out |
| Back | The same art again (stem, calyx, leaf, highlight), his credit, "krux was here", a base64 line with 16 short strokes | Art kept. **His credit moved 1.6 mm, "krux was here" 12.4 mm, both unchanged.** **The base64 line and its strokes stay exactly where he put them, which is now under the SAO connector's plastic shroud** (owner decision, below). Labels added: "EGGPLANT rA", "SAO++", "NO USB ON SAO", switch ends (SAO / USB), "+"/"−" and "LiPo" at the socket, "1" at the connector |
| Dropped | — | ATtiny85, its 10 k reset pull-up, his two 10 k I2C pull-ups (SAO++ boards leave the pull-ups to the badge), two 0 Ω links, the six programming pads |

**Parts shared with the rest of SAO++:** connector, switch, XIAO footprint, LiPo socket, the 330 Ω and 1.3 k resistors. **New, kept in this board's folder:** only the maker's two-colour LED, on his own land pattern. His BOM calls it "PHBM2012QBDSURKC" (a Kingbright-style blue/hyper-red 0805 part); the exact catalogue number and an LCSC source still have to be found.

## Why it is 35 % bigger (owner rule of 2026-11-12)

At the maker's size the only spot where the XIAO (21 × 18 mm, plus its pads) fits with its USB-C at an edge is the whole round bottom of the eggplant, and then the connector, switch and LiPo socket have nowhere to go. A search over every angle and position at 1.30× found room for the XIAO and the connector but never for the switch and the LiPo socket as well; **1.35× is the smallest step that fits all four**, with the XIAO's USB-C coming out of the left-hand side, where the outline is straight enough that no flattening is needed. Area is 1.8× the original. Lettering and line widths only get bigger.

What scaling did **not** fix: the bulb is still crowded, so four of the five LEDs and two of his three pieces of lettering had to move (below), and the board needs a few vias.

## The LEDs: where they are now

All five are the maker's part, on the back, facing away from the board as on his. Compared with his positions (scaled): LED2 is where he put it (in the light stripe); LED1 is 10.8 mm higher (the connector now covers his spot), LED3 8.5 mm up-left of his (the switch), LED4 6 mm lower (the XIAO), LED5 13.4 mm to the left (his credit and the LiPo socket). Each sits with its two resistors right beside it.

## LED current

His 22 Ω resistors let each colour draw tens of milliamps, limited only by the ATtiny's pins. SAO++ uses its two shared values instead: **blue through 330 Ω (about 1.5 mA per LED), red through 1.3 k (about 1.1 mA per LED)**, so one XIAO pin never feeds more than about 8 mA. All ten on: about 13 mA. That is in the range the house uses for LEDs lit from behind; it will be dimmer than his. If the first board is too dim, the resistors can be lowered (330 Ω on red gives about 4 mA each, 21 mA on one pin, still within the pin's rating).

**Which colour is which** is not certain: his schematic wires ATtiny pin PB3 to the anodes his LED footprint names "blue", but his sketch calls PB3 "red". This board follows the footprint's names (pad AB = blue gets 330 Ω on D3, pad AR = red gets 1.3 k on D2). The first board shows which is right; if the colours are swapped, swap the two resistor values and one line of firmware.

## How the power switch works

| Knob | Badge 3.3 V | What runs the board |
|---|---|---|
| **SAO** (toward the "SAO" label on the back) | connected to the XIAO's 3V3 pin | the badge |
| **OFF** (middle) | disconnected | nothing from the badge; if USB or a LiPo is attached, the switch pulls D1 high (through 330 Ω) and the firmware goes dark and sleeps |
| **USB-BAT** (toward "USB") | disconnected | the XIAO, from USB-C or the LiPo |

- **Do not plug in USB while the knob is on SAO and the board is on a badge.** Two 3.3 V regulators would be joined. It is printed on the back.
- **OFF is a sleep, not a hard cut, when a LiPo is attached.** Unplug the cell for storage.
- **Feeding the XIAO through its 3V3 pin** is how badge power reaches it, as on every SAO++ XIAO board; Seeed documents that pin as an output only. First thing to test.

## How it is wired

The back carries everything. On one copper layer the lines cross each other in nine places (the connector sits above the XIAO, the switch and battery on the right, and five LEDs all round, each needing both colour lines), so those nine crossings are made with **short links on the front, under the solder mask, each between two covered holes (vias)**: 18 vias. They sit in the dark copper body, never in the gold stem or the light stripe, and show only as faint lines under the mask (visible in the front render). The back ground copper is in 15 separate pieces; **15 more covered vias** join each piece to the front copper body, which is ground (as it was on the maker's board). In total 33 vias, all 0.3 mm holes covered by mask on both sides. The routing is done by `hardware/router.py` (a small router with hard time and rip-up limits).

## Pin map

| XIAO pin | Goes to |
|---|---|
| D2 | the five red anodes, through 1.3 k each. D2 rather than the house LED pin D10 so the two colour lines leave the module side by side; on the three modules D2 is a start-up pin only for the S3's JTAG choice, which is ignored unless a fuse is burnt |
| D3 | the five blue anodes, through 330 Ω each |
| D4 / D5 | SAO SDA / SCL (no pull-ups on the board). The XIAO is the badge's I2C **target**, address 0x28 (0x36, the maker's, as a firmware option) |
| D7 / D6 | SAO GPIO1 / GPIO2, each through 330 Ω (R2 / R3) |
| D1 | switch OFF sense, through R1 (330 Ω): high when the knob is on OFF |
| 3V3, GND | the board's 3.3 V rail (switch common) and ground |
| BAT+ / BAT− (under the module, both positions) | the JST-PH LiPo socket |
| D0, D8, D9, D10, 5V | not connected |
| BOOT button (on the module) | mode button |

## Firmware

New Rust firmware is in [`firmware/`](firmware/): his five light shows plus "off", his I2C commands and memory map, and his infection game, at address 0x28 (or his 0x36 as a build option). 31 tests pass on a PC and it builds for the C3, C6 and S3; **it has never run on a real board**, and one feature is missing: the name, mode and infections are not yet kept through a power-off. The maker's Arduino sketch, his protocol notes and his EEPROM script are in `original/dc26-sao/`.

## Decisions for the owner

1. **The base64 line and its strokes** ("dGhpcyBpcy BiYXNlNjQK", which decodes to "this is base64", with 16 short strokes over it) sit exactly where the maker put them, but the SAO connector now stands on that spot, so they are printed under its shroud and cannot be seen. No other spot on the back is big enough. Options: accept (as Do Or Donut's hidden logos), or move them to the back of the calyx, which means giving up part of the back's copy of his calyx art.
2. **His credit and "krux was here" are printed with his own thin strokes** (8 % of the letter height: 0.10 mm and 0.07 mm on this board). KiCad warns that 0.07 mm is below its 0.08 mm minimum, and many board houses print nothing under about 0.15 mm. They are kept exactly as he set them; thickening them to 0.15 mm would keep size, font and wording.
3. **The 45° tilt.** The connector is turned 45° as the maker had it, so the eggplant hangs leaning when worn. Turning it upright is one number in `hardware/build_board.py` but means re-routing and re-checking.

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
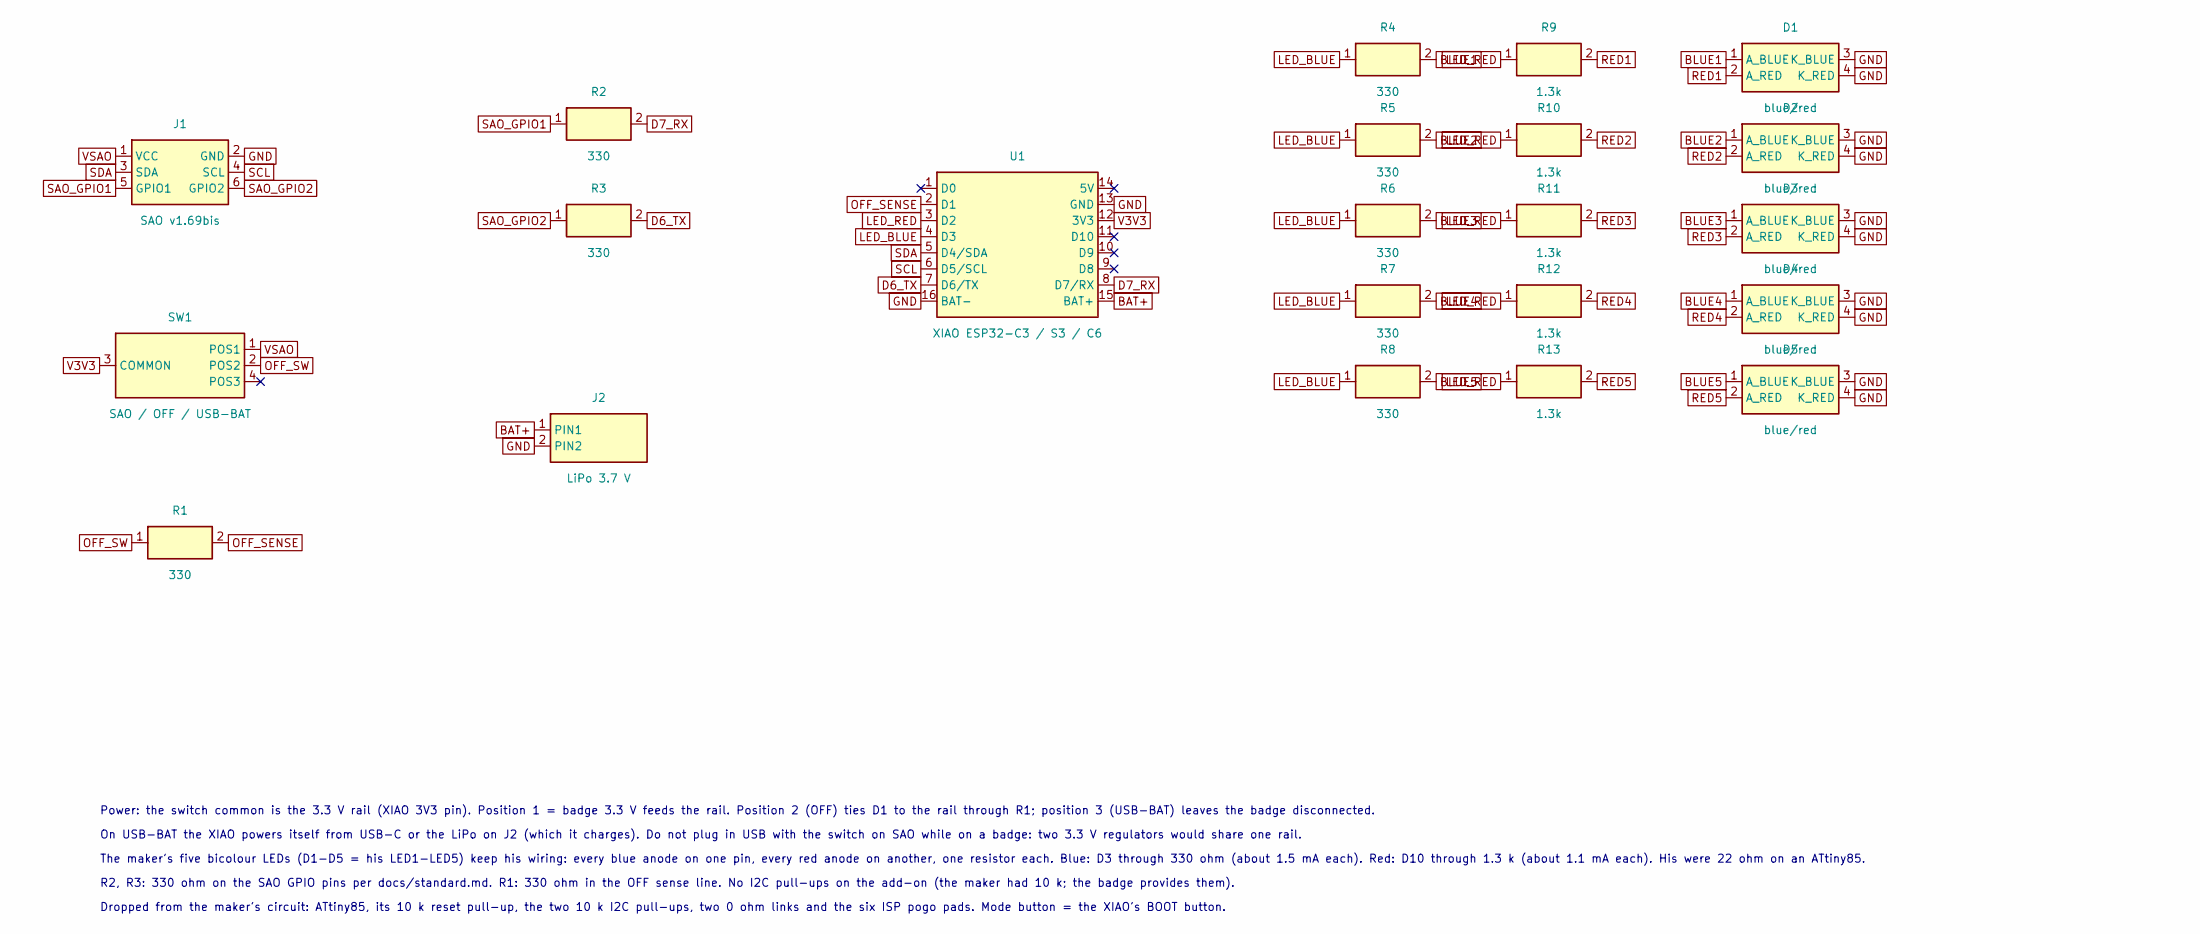
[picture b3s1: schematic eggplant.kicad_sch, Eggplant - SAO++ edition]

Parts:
D1, D2, D3, D4, D5: blue/red; LED_Bicolour_0805; MPN APHBM2012QBDSURKC; LCSC C5568785
J1: SAO v1.69bis; SAOPP_CONN-01_BoxHeader_2x03_P2.54mm_SMD_XFCN_BH254VS-6P; MPN BH254VS-6P; LCSC C492445
J2: LiPo 3.7 V; SAOPP_CONN-10_JST_PH_S2B-PH-SM4-TB_1x02_Horizontal; MPN S2B-PH-SM4-TB(LF)(SN); LCSC C295747
R1, R2, R3, R4, R5, R6, R7, R8: 330; SAOPP_R_0603_1608Metric; MPN 0603WAF3300T5E; LCSC C23138
R9, R10, R11, R12, R13: 1.3k; SAOPP_R_0603_1608Metric; MPN 0603WAF1301T5E; LCSC C22767
SW1: SAO / OFF / USB-BAT; SAOPP_SW-01_Slide_SP3T_CK_PCM13SMTR; MPN PCM13SMTR; LCSC C221842
U1: XIAO ESP32-C3 / S3 / C6; SAOPP_MCU-01_Seeed_XIAO_SMD_C3_S3_C6; MPN XIAO ESP32-C3 / S3 / C6

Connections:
BAT+: J2.1 (PIN1), U1.15 (BAT+)
BLUE1: D1.1 (A_BLUE), R4.2
BLUE2: D2.1 (A_BLUE), R5.2
BLUE3: D3.1 (A_BLUE), R6.2
BLUE4: D4.1 (A_BLUE), R7.2
BLUE5: D5.1 (A_BLUE), R8.2
D6_TX: R3.2, U1.7 (D6/TX)
D7_RX: R2.2, U1.8 (D7/RX)
GND: D1.3 (K_BLUE), D1.4 (K_RED), D2.3 (K_BLUE), D2.4 (K_RED), D3.3 (K_BLUE), D3.4 (K_RED), D4.3 (K_BLUE), D4.4 (K_RED), D5.3 (K_BLUE), D5.4 (K_RED), J1.2 (GND), J2.2 (PIN2), U1.13 (GND), U1.16 (BAT-)
LED_BLUE: R4.1, R5.1, R6.1, R7.1, R8.1, U1.4 (D3)
LED_RED: R9.1, R10.1, R11.1, R12.1, R13.1, U1.3 (D2)
OFF_SENSE: R1.2, U1.2 (D1)
OFF_SW: R1.1, SW1.2 (POS2)
RED1: D1.2 (A_RED), R9.2
RED2: D2.2 (A_RED), R10.2
RED3: D3.2 (A_RED), R11.2
RED4: D4.2 (A_RED), R12.2
RED5: D5.2 (A_RED), R13.2
SAO_GPIO1: J1.5 (GPIO1), R2.1
SAO_GPIO2: J1.6 (GPIO2), R3.1
SCL: J1.4 (SCL), U1.6 (D5/SCL)
SDA: J1.3 (SDA), U1.5 (D4/SDA)
V3V3: SW1.3 (COMMON), U1.12 (3V3)
VSAO: J1.1 (VCC), SW1.1 (POS1)

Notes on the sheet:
Power: the switch common is the 3.3 V rail (XIAO 3V3 pin). Position 1 = badge 3.3 V feeds the rail. Position 2 (OFF) ties D1 to the rail through R1; position 3 (USB-BAT) leaves the badge disconnected.
On USB-BAT the XIAO powers itself from USB-C or the LiPo on J2 (which it charges). Do not plug in USB with the switch on SAO while on a badge: two 3.3 V regulators would share one rail.
The maker's five bicolour LEDs (D1-D5 = his LED1-LED5) keep his wiring: every blue anode on one pin, every red anode on another, one resistor each. Blue: D3 through 330 ohm (about 1.5 mA each). Red: D10 through 1.3 k (about 1.1 mA each). His were 22 ohm on an ATtiny85.
R2, R3: 330 ohm on the SAO GPIO pins per docs/standard.md. R1: 330 ohm in the OFF sense line. No I2C pull-ups on the add-on (the maker had 10 k; the badge provides them).
Dropped from the maker's circuit: ATtiny85, its 10 k reset pull-up, the two 10 k I2C pull-ups, two 0 ohm links and the six ISP pogo pads. Mode button = the XIAO's BOOT button.

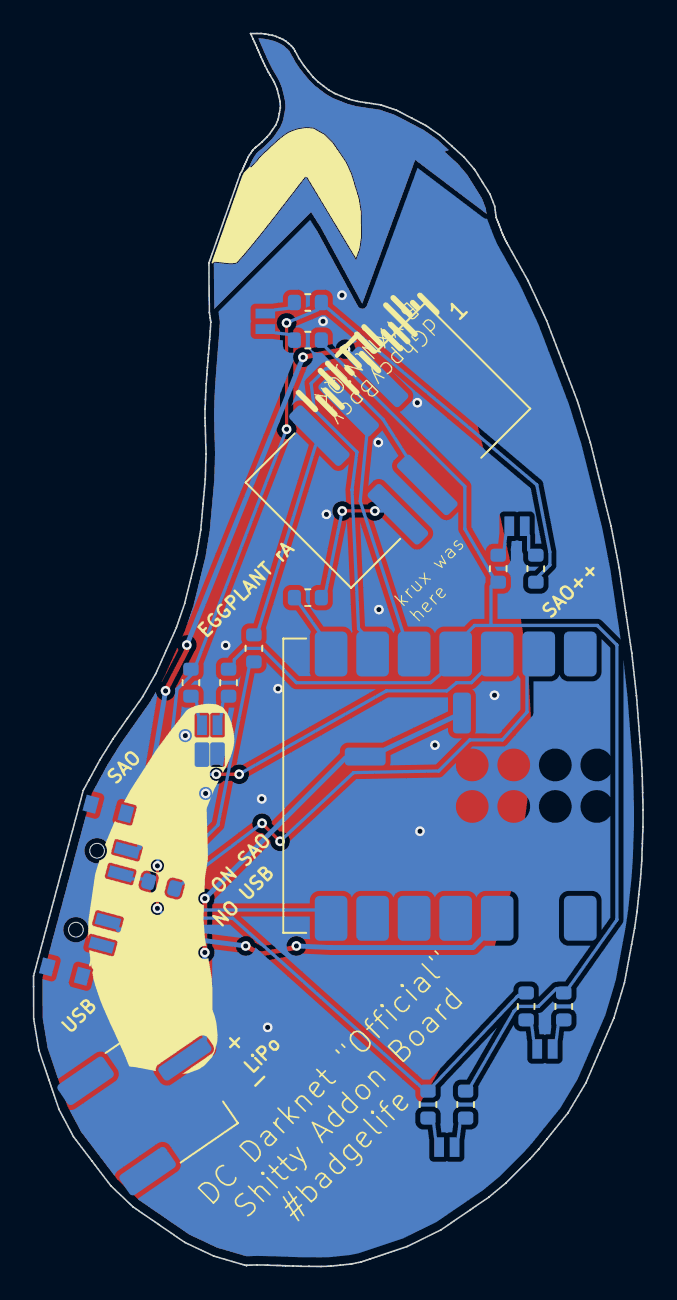
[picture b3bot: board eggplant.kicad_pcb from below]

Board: 2 copper layers, 37.3 x 75.4 mm, 22 parts (22 on the bottom side), 24 nets.

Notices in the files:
boards/mad-cat-backpack/hardware/mad-cat-backpack.kicad_pcb:
Original design: Peter Shabino (Wireb), 2018, github.com/Wireb/Mad_Cat_Backpack, MIT license
boards/sao-jack/hardware/sao-jack.kicad_pcb:
Original design: hamster, DEF CON 30 SAO Jack 1.0 (2022), MIT license, github.com/hamster/defcon30
boards/sao-nunchuck/hardware/sao-nunchuck.kicad_pcb:
Original design: Andy and Jared Geppert (ageppert), SAO Nunchuck V1.0, 2024, MIT license, github.com/ageppert/SAO_Nunchuck
